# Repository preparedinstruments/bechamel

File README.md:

# Lo-Fi FPGA Video Art Board

A Lattice iCE40HX1K-based FPGA developement board for lo-fi, live-playable video experiments ranging from the gnarly/migraine-inducing all the way to the accidentally enjoyable.

|                          |                          |
:-------------------------:|:-------------------------:
  | 

# Features :

**WARNING: This video may potentially trigger seizures for people with photosensitive epilepsy. Viewer discretion is advised.**

https://github.com/user-attachments/assets/2b71dbfc-7b5e-4651-8198-416c93c0dd36

- 640x480 60Hz HDMI and VGA out, takes raspberry pi video in in DPI mode (https://pinout.xyz/pinout/dpi)
- 9-key mechanical button interface on a hand-solderable, low-cost, single-board design
- 100MHz clock and a 256K x 8 bit external SRAM for screen buffer(s)
- Connections for raspberry pi flash programming

# PCB files

[KiCAD and Eagle PCBs](https://github.com/preparedinstruments/bechamel/tree/main/PCB)

# BOM :

[Excel BOM Mouser / Digikey ](https://github.com/preparedinstruments/bechamel/tree/main/BOM)

- 9x Mechanical keyboard keys
- 1x FPGA iCE40HX1K-TQ144
- 1x 100MHz clock oscillator
- 1x SRAM 2Mb 256Kx8
- 1x Flash N25Q032A13ESC40F
- 1x USB-C SMD 6 pin connector
- 1x 3.3V reg TLV73333PDBVT 
- 1x 1.2V reg TLV73312PDBVT
- 1x PFET
- 1x Resettable Fuse
- 1x D-SUB 15 connector
- 1x HDMI Connector 
- 50x 0.1µF capacitor 0805
- 50x  10kΩ, 1.8kΩ, 1kΩ, 470Ω, 270Ω, 120Ω resistors 0805
- 5x LEDs 0805
- 2x Dual-row headers

optional extras : (1x Raspberry Pi Zero, 1x Micro SD holder, 1x 10kΩ potentiometers)

# HDL files

[Verilog and Pin constraints files ](https://github.com/preparedinstruments/bechamel/tree/main/verilog)

To synthesize files :

[Yoysis Open-source Toolchain ](https://github.com/YosysHQ/yosys)

...or, request an iCEcube2 licence from Lattice :

[iCEcube2 Toolchain](https://www.latticesemi.com/iCEcube2)

To program flash memory you can use raspberry pi using these OLIMEX resources :

- https://www.olimex.com/wiki/ICE40HX1K-EVB#Get_started_under_Linux
- https://github.com/anse1/olimex-ice40-notes

# Raspberry Pi DPI config file

This config file sets the rpi in DPI mode at 50MHz. It can work with the rpi video pass thru verilog file.

[config.txt](https://github.com/preparedinstruments/bechamel/tree/main/raspberry_pi)

# FAQ

Q: How dare you release into the wild verilog code this hideous ?

A: Spank me daddy.

Q: Is this even art ?

A: I can't believe it's not butter! 

# Acknowledgements

**Verilog** :

Mike Field <hamster@snap.net.nz> for his minimalDVID_encoder.vhd : A quick and dirty DVI-D implementation (https://gist.github.com/uXeBoy/0d46e2f1560f73dd573d83e78309bfa0)

Iñigo Muguruza (imuguruza) for his VGA sync code : https://github.com/imuguruza/alhambra_II_test/blob/master/vga/vga_test/vga_sync.v

NightMachines on Bytebeats : https://llllllll.co/t/bytebeats-a-beginner-s-guide/16491

General verilog learning from HDL Bits : https://hdlbits.01xz.net/wiki/Main_Page

**FPGA Hardware design** :

OLIMEX FPGA dev board : https://github.com/OLIMEX/iCE40HX1K-EVB/tree/master

Alhambra II FPGA dev board : https://github.com/FPGAwars/Alhambra-II-FPGA/tree/master

# TODO

Get SD card reading functional

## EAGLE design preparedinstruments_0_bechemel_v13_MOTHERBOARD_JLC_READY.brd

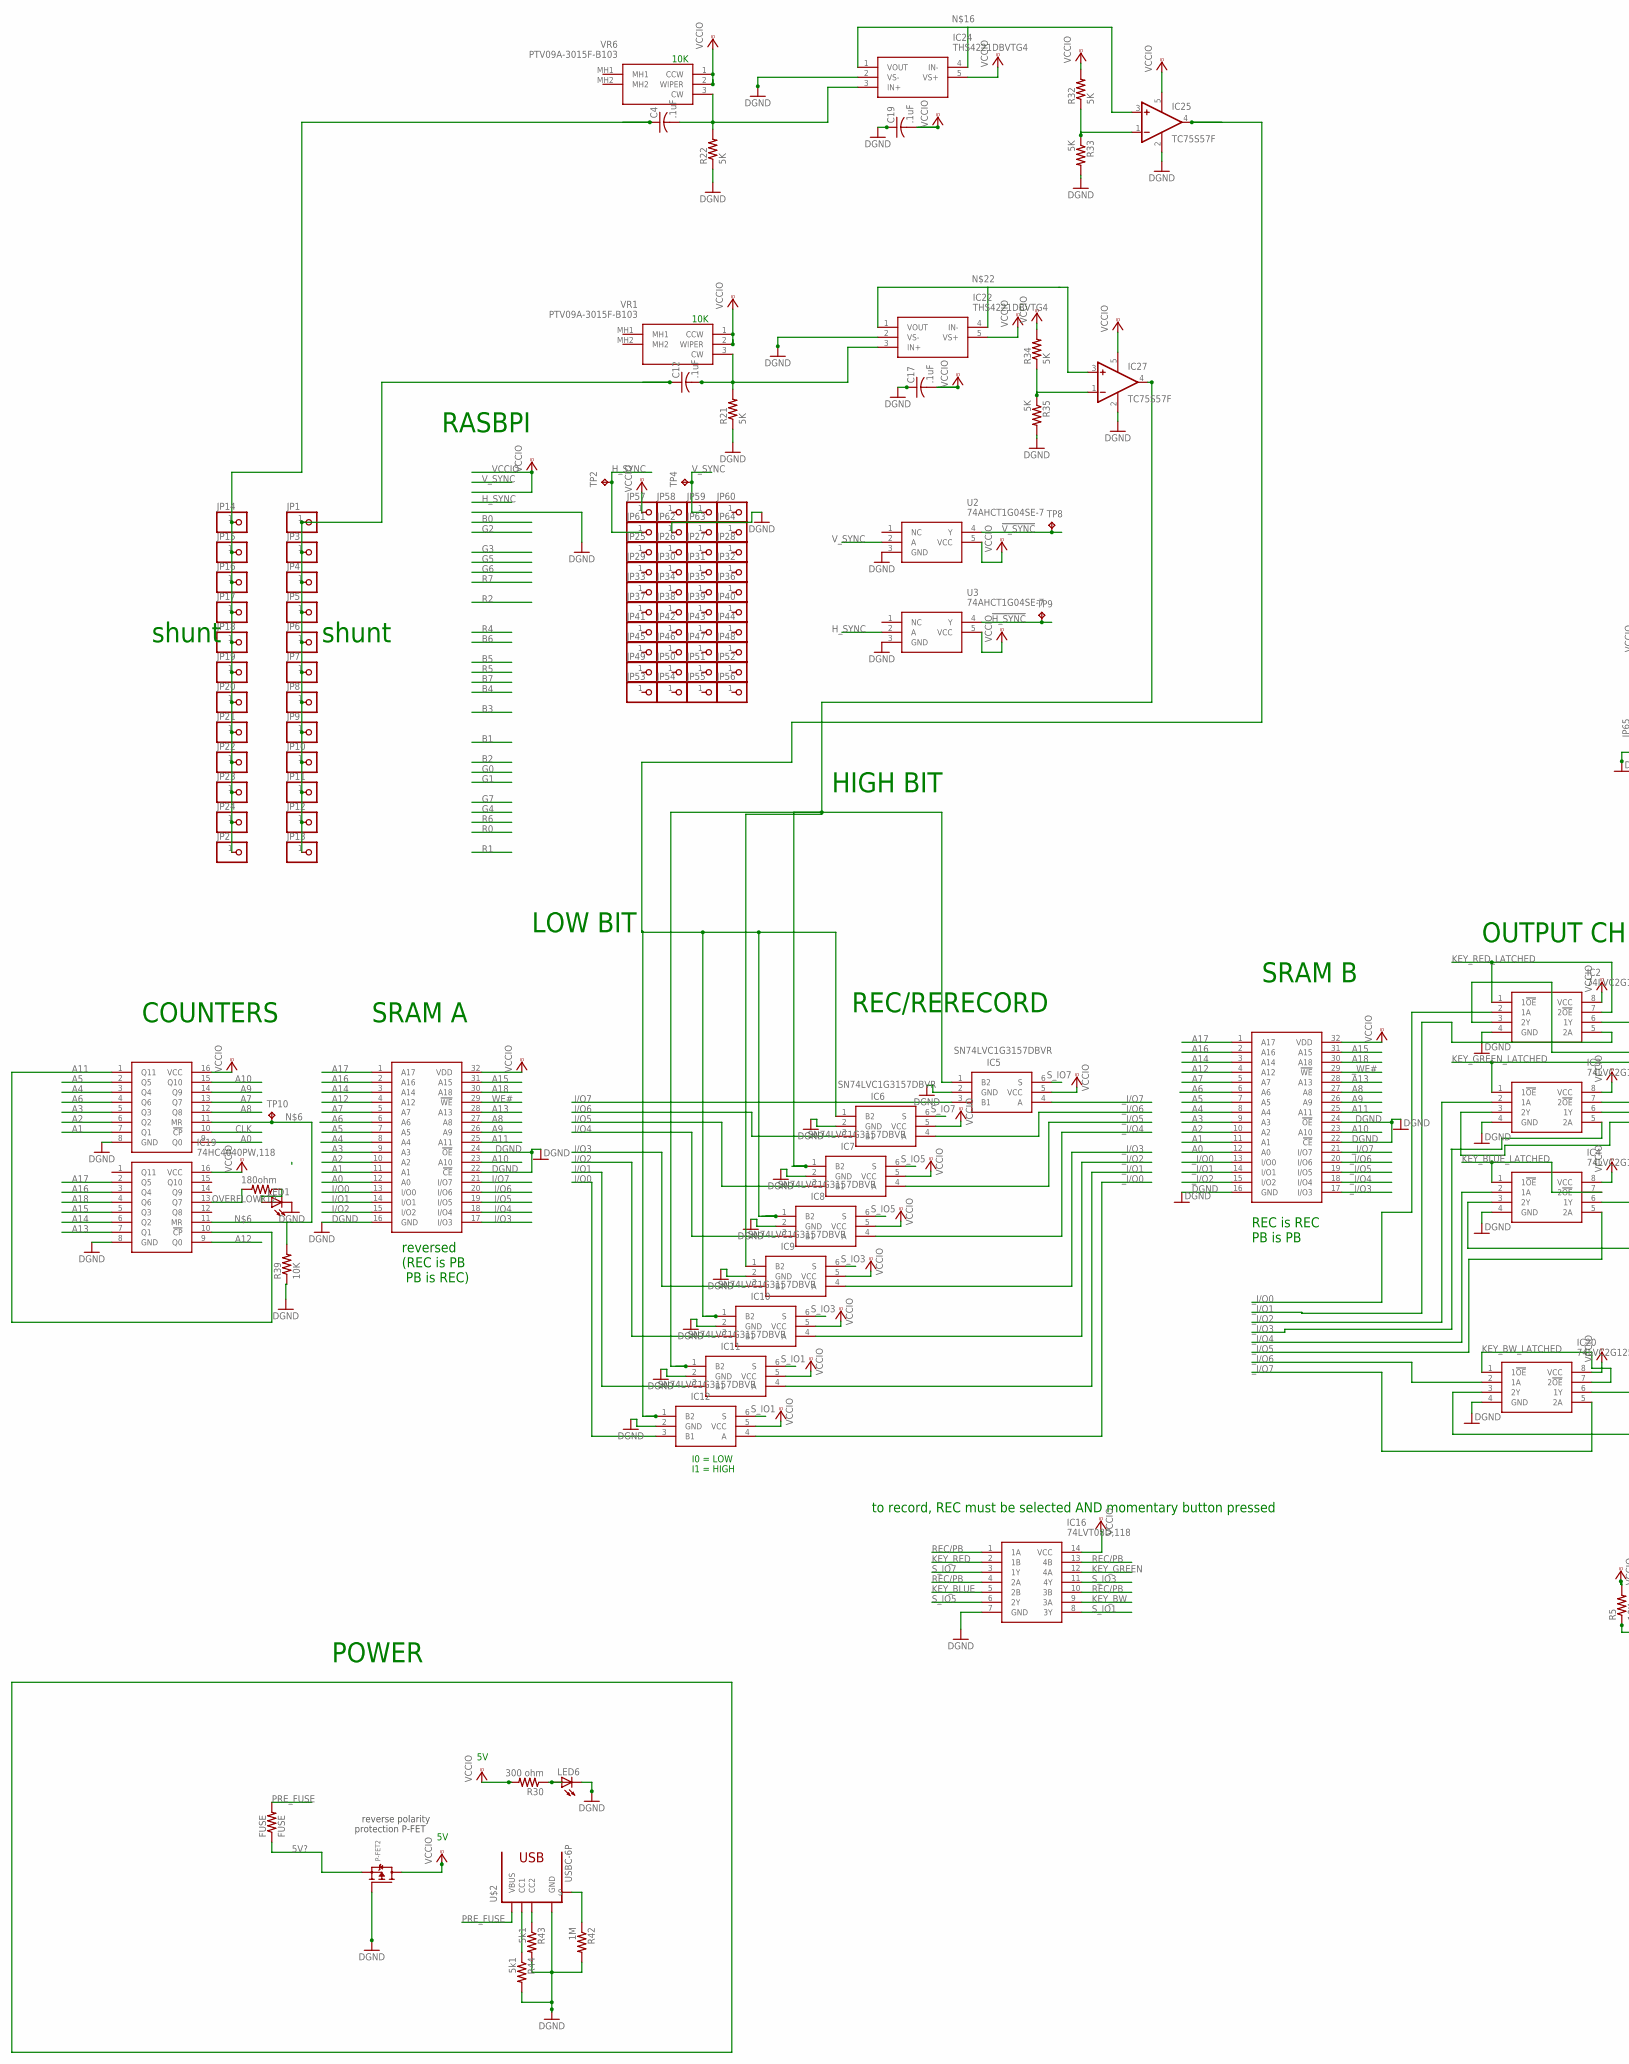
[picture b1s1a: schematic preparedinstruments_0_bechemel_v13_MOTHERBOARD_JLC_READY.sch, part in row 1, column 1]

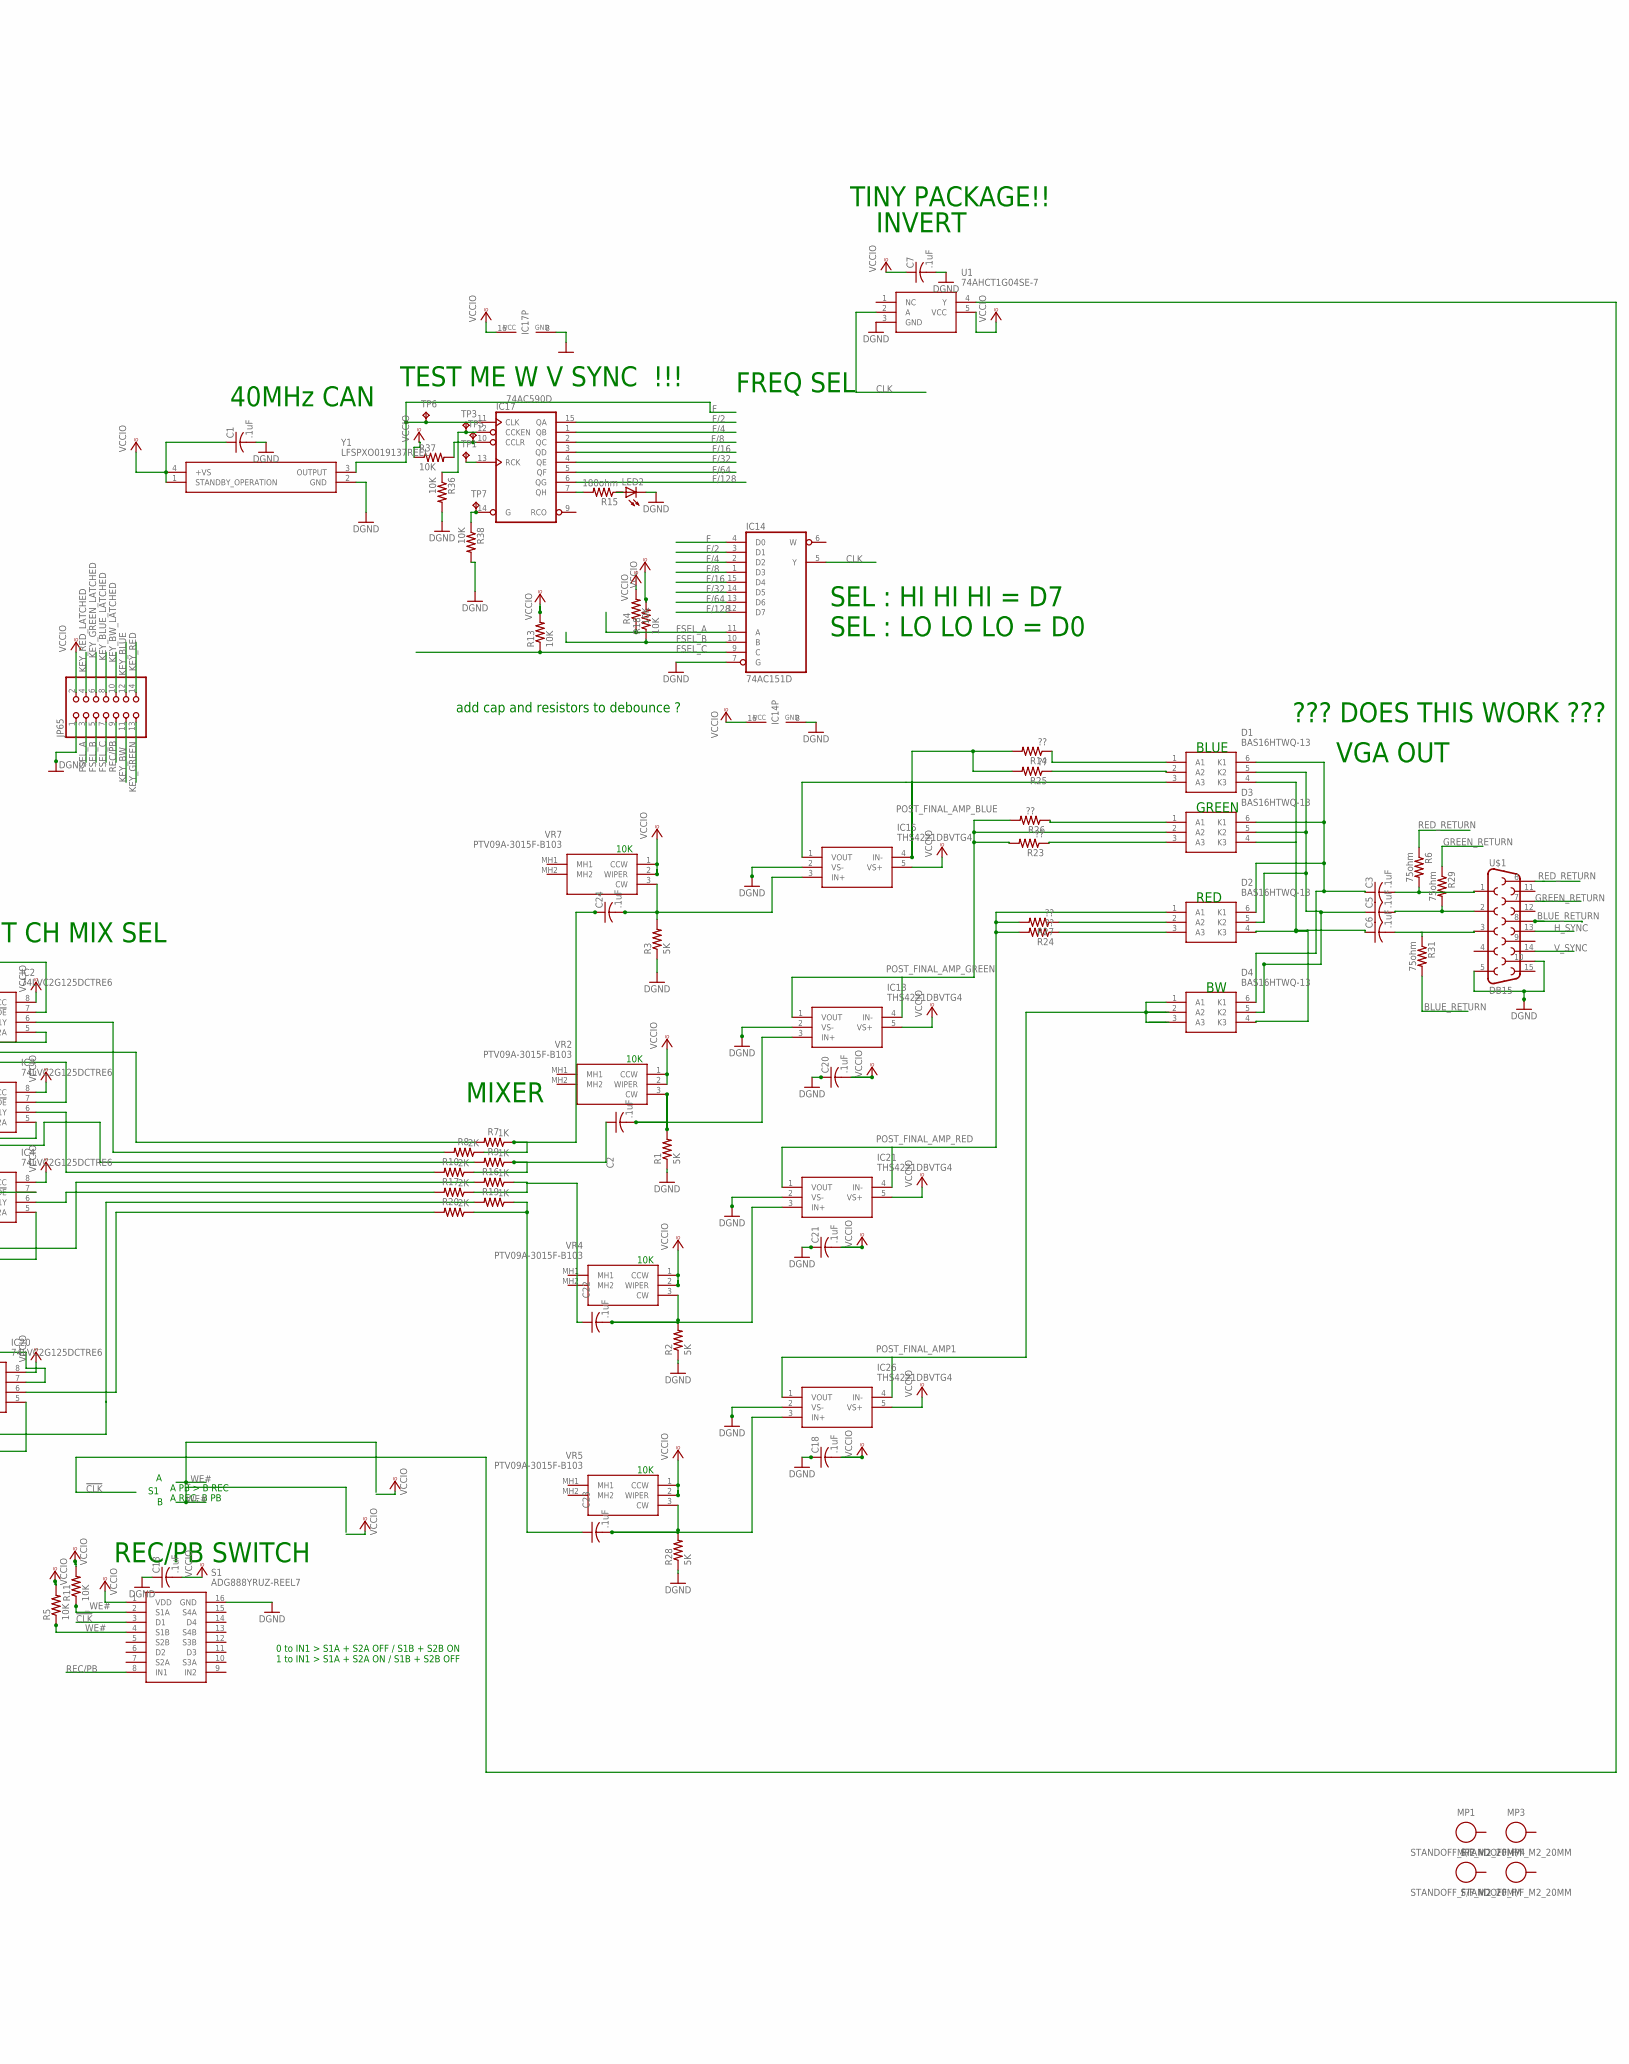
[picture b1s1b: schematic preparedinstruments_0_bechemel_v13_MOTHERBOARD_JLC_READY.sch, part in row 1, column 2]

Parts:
C1, C2, C3, C4, C5, C6, C7, C12, C13, C17, C18, C19, C20, C21, C22, C23, C24: .1uF; C0805
D1, D2, D3, D4: BAS16HTWQ-13; SOT65P210X110-6N
FUSE: FUSE; R0805
IC1, IC23: IS61C5128AS-25QLI; SOIC127P1412X305-32N
IC2, IC3, IC4, IC20: 74LVC2G125DCTRE6; SOP65P400X130-8N
IC5, IC6, IC7, IC8, IC9, IC10, IC11, IC12: SN74LVC1G3157DBVR; SOT95P280X145-6N
IC13, IC15, IC21, IC22, IC24, IC26: THS4221DBVTG4; SOT95P280X145-5N
IC14: 74AC151D; SO16
IC16: 74LVT08D,118; 74LVT08D118
IC17: 74AC590D; SO16
IC18, IC19: 74HC4040PW,118; SOP65P640X110-16N
IC25, IC27: TC75S57F; DBV-R-PDSO-G5
JP1, JP2, JP3, JP4, JP5, JP6, JP7, JP8, JP9, JP10, JP11, JP12, JP13, JP14, JP15, JP16, JP17, JP18, JP19, JP20, JP21, JP22, JP23, JP24, JP25, JP26, JP27, JP28, JP29, JP30, JP31, JP32, JP33, JP34, JP35, JP36, JP37, JP38, JP39, JP40, JP41, JP42, JP43, JP44, JP45, JP46, JP47, JP48, JP49, JP50, JP51, JP52, JP53, JP54, JP55, JP56, JP57, JP58, JP59, JP60, JP61, JP62, JP63, JP64: PINHD-1X1; 1X01
JP65: PINHD-2X7; 2X07
LED1, LED2, LED6: LEDCHIPLED_0805; CHIPLED_0805
MP1, MP2, MP3, MP4: STANDOFF_F/F_M2_20MM; STANDOFF_HEX_FEMALE_400X2000_M2X0.4_MTGP600H220
P-FET2: MOSFET-PWIDE; SOT23-WIDE
R1, R2, R3, R21, R22, R28, R32, R33, R34, R35: 5K; R0805
R4, R5, R11, R13, R18, R36, R37, R38, R39: 10K; R0805
R6, R29, R31: 75ohm; R0805
R7, R9, R16, R19: 1K; R0805
R8, R10, R17, R20: 2K; R0805
R12, R15: 180ohm; R0805
R14, R23, R24, R25, R26, R27: ??; R0805
R30: 300 ohm; R0805
R42: 1M; R0805
R43, R44: 5k1; R0805
S1: ADG888YRUZ-REEL7; SOP65P640X120-16N
TP1, TP2, TP3, TP4, TP5, TP6, TP7, TP8, TP9, TP10: TPB1,27; B1,27
U1, U2, U3: 74AHCT1G04SE-7; SOT65P210X110-5N
U$1: DB15
U$2: USBC-6P; USCX-06FX-XXMX-01
VR1, VR2, VR4, VR5, VR6, VR7: PTV09A-3015F-B103; PTV09A3015FB103
Y1: LFSPXO019137REEL

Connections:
5V?: FUSE.1, P-FET2.2 (S)
!CLK: S1.3 (D1), U1.4 (Y)
!H_SYNC: TP9.TP, U3.4 (Y)
!V_SYNC: TP8.TP, U2.4 (Y)
A0: IC1.12 (A0), IC18.9 (Q0), IC23.12 (A0)
A1: IC1.11 (A1), IC18.7 (Q1), IC23.11 (A1)
A2: IC1.10 (A2), IC18.6 (Q2), IC23.10 (A2)
A3: IC1.9 (A3), IC18.5 (Q3), IC23.9 (A3)
A4: IC1.8 (A4), IC18.3 (Q4), IC23.8 (A4)
A5: IC1.7 (A5), IC18.2 (Q5), IC23.7 (A5)
A6: IC1.6 (A6), IC18.4 (Q6), IC23.6 (A6)
A7: IC1.5 (A7), IC18.13 (Q7), IC23.5 (A7)
A8: IC1.27 (A8), IC18.12 (Q8), IC23.27 (A8)
A9: IC1.26 (A9), IC18.14 (Q9), IC23.26 (A9)
A10: IC1.23 (A10), IC18.15 (Q10), IC23.23 (A10)
A11: IC1.25 (A11), IC18.1 (Q11), IC19.10 (!CP), IC23.25 (A11)
A12: IC1.4 (A12), IC19.9 (Q0), IC23.4 (A12)
A13: IC1.28 (A13), IC19.7 (Q1), IC23.28 (A13)
A14: IC1.3 (A14), IC19.6 (Q2), IC23.3 (A14)
A15: IC1.31 (A15), IC19.5 (Q3), IC23.31 (A15)
A16: IC1.2 (A16), IC19.3 (Q4), IC23.2 (A16)
A17: IC1.1 (A17), IC19.2 (Q5), IC23.1 (A17)
A18: IC1.30 (A18), IC19.4 (Q6), IC23.30 (A18)
BLUE_RETURN: R31.2, U$1.8
CLK: IC14.5 (Y), IC18.10 (!CP), U1.2 (A)
COMP2_OUT: IC6.1 (B2), IC8.1 (B2), IC10.1 (B2), IC12.1 (B2), IC25.4 (OUT)
DGND: C1.2, C7.2, C13.1, C17.1, C18.1, C19.1, C20.1, C21.1, IC1.16 (GND), IC1.22 (!CE), IC1.24 (!OE), IC2.4 (GND), IC3.4 (GND), IC4.4 (GND), IC5.2 (GND), IC6.2 (GND), IC7.2 (GND), IC8.2 (GND), IC9.2 (GND), IC10.2 (GND), IC11.2 (GND), IC12.2 (GND), IC13.2 (VS-), IC14.7 (G), IC14.8 (GND), IC15.2 (VS-), IC16.7 (GND), IC17.8 (GND), IC18.8 (GND), IC19.8 (GND), IC20.4 (GND), IC21.2 (VS-), IC22.2 (VS-), IC23.16 (GND), IC23.22 (!CE), IC23.24 (!OE), IC24.2 (VS-), IC25.2 (GND), IC26.2 (VS-), IC27.2 (GND), JP62.1, JP65.1, LED1.C, LED2.C, LED6.C, P-FET2.1 (G), R1.1, R2.1, R3.1, R21.1, R22.1, R28.1, R33.2, R35.2, R36.2, R38.2, R39.1, R42.2, R43.2, R44.2, S1.16 (GND), U1.3 (GND), U2.3 (GND), U3.3 (GND), U$1.5, U$1.10, U$2.GND1 (GND), U$2.GND2 (GND), Y1.2 (GND)
F: IC14.4 (D0), IC17.11 (CLK), TP6.TP, Y1.3 (OUTPUT)
F/2: IC14.3 (D1), IC17.15 (QA)
F/4: IC14.2 (D2), IC17.1 (QB)
F/8: IC14.1 (D3), IC17.2 (QC)
F/16: IC14.15 (D4), IC17.3 (QD)
F/32: IC14.14 (D5), IC17.4 (QE)
F/64: IC14.13 (D6), IC17.5 (QF)
F/128: IC14.12 (D7), IC17.6 (QG)
FSEL_A: IC14.11 (A), JP65.3, R4.1
FSEL_B: IC14.10 (B), JP65.5, R18.1
FSEL_C: IC14.9 (C), JP65.7, R13.1
GREEN_RETURN: R29.1, U$1.7
H_SYNC: JP61.1, TP2.TP, U3.2 (A), U$1.13
I/O0: IC12.3 (B1), IC23.13 (I/O0)
I/O1: IC11.3 (B1), IC23.14 (I/O1)
I/O2: IC10.3 (B1), IC23.15 (I/O2)
I/O3: IC9.3 (B1), IC23.17 (I/O3)
I/O4: IC8.3 (B1), IC23.18 (I/O4)
I/O5: IC7.3 (B1), IC23.19 (I/O5)
I/O6: IC6.3 (B1), IC23.20 (I/O6)
I/O7: IC5.3 (B1), IC23.21 (I/O7)
INT_IN1: C24.2, IC15.3 (IN+), R3.2, VR7.3 (CW)
INT_IN2: C12.2, IC22.3 (IN+), R21.2, VR1.3 (CW)
INT_IN3: C4.2, IC24.3 (IN+), R22.2, VR6.3 (CW)
INT_IN4: C22.2, IC21.3 (IN+), R2.2, VR4.3 (CW)
INT_IN5: C23.2, IC26.3 (IN+), R28.2, VR5.3 (CW)
INT_IN6: C2.2, IC13.3 (IN+), R1.2, VR2.3 (CW)
KEY_BLUE: IC16.5 (2B), JP65.12
KEY_BLUE_LATCHED: IC4.1 (1!OE), IC4.7 (2!OE), JP65.8
KEY_BW: IC16.9 (3A), JP65.11
KEY_BW_LATCHED: IC20.1 (1!OE), IC20.7 (2!OE), JP65.10
KEY_GREEN: IC16.12 (4A), JP65.13
KEY_GREEN_LATCHED: IC3.1 (1!OE), IC3.7 (2!OE), JP65.6
KEY_RED: IC16.2 (1B), JP65.14
KEY_RED_LATCHED: IC2.1 (1!OE), IC2.7 (2!OE), JP65.4
unnamed: LED2.A, R15.1
unnamed: C3.2, R6.2, U$1.1
unnamed: C12.1, JP1.1, JP3.1, JP4.1, JP5.1, JP6.1, JP7.1, JP8.1, JP9.1, JP10.1, JP11.1, JP12.1, JP13.1
unnamed: LED1.A, R12.1
unnamed: IC17.7 (QH), R15.2
unnamed: IC18.11 (MR), IC19.11 (MR), R39.2, TP10.TP
unnamed: IC4.3 (2Y), R16.2
unnamed: C5.2, R29.2, U$1.2
unnamed: LED6.A, R30.1
unnamed: IC4.6 (1Y), R17.2
unnamed: C6.2, R31.1, U$1.3
unnamed: R43.1, U$2.CC2
unnamed: IC25.1 (-IN), R32.1, R33.1
unnamed: IC24.1 (VOUT), IC24.4 (IN-), IC25.3 (+IN)
unnamed: IC20.3 (2Y), R19.2
unnamed: R42.1, U$2.SHIELD1 (S), U$2.SHIELD2 (S), U$2.SHIELD3 (S), U$2.SHIELD4 (S)
unnamed: IC27.1 (-IN), R34.1, R35.1
unnamed: IC20.6 (1Y), R20.2
unnamed: R44.1, U$2.CC1
unnamed: IC22.1 (VOUT), IC22.4 (IN-), IC27.3 (+IN)
unnamed: IC17.12 (CCKEN), R36.1, TP3.TP
unnamed: IC2.3 (2Y), R7.2
unnamed: IC2.6 (1Y), R8.2
unnamed: IC3.3 (2Y), R9.2
unnamed: IC3.6 (1Y), R10.2
unnamed: C4.1, JP2.1, JP14.1, JP15.1, JP16.1, JP17.1, JP18.1, JP19.1, JP20.1, JP21.1, JP22.1, JP23.1, JP24.1
unnamed: IC17.13 (RCK), TP1.TP
unnamed: IC17.10 (CCLR), R37.2, TP5.TP
unnamed: C24.1, R7.1, R8.1
unnamed: C22.1, R16.1, R17.1
unnamed: C2.1, R9.1, R10.1
unnamed: C23.1, R19.1, R20.1
unnamed: D3.1 (A1), R26.1
unnamed: D1.1 (A1), R14.1
unnamed: D1.2 (A2), R25.1
unnamed: D2.3 (A3), R24.1
unnamed: C3.1, D1.6 (K1), D2.6 (K1), D3.6 (K1), D4.6 (K1)
unnamed: IC17.14 (G), R38.1, TP7.TP
unnamed: D2.2 (A2), R27.1
unnamed: D3.3 (A3), R23.1
unnamed: C5.1, D1.5 (K2), D2.5 (K2), D3.5 (K2), D4.5 (K2)
unnamed: C6.1, D1.4 (K3), D2.4 (K3), D3.4 (K3), D4.4 (K3)
OVERFLOW: IC19.13 (Q7), R12.2
POST_FINAL_AMP1: D4.1 (A1), D4.2 (A2), D4.3 (A3), IC26.1 (VOUT), IC26.4 (IN-)
POST_FINAL_AMP_BLUE: D1.3 (A3), IC15.1 (VOUT), IC15.4 (IN-), R14.2, R25.2
POST_FINAL_AMP_GREEN: D3.2 (A2), IC13.1 (VOUT), IC13.4 (IN-), R23.2, R26.2
POST_FINAL_AMP_RED: D2.1 (A1), IC21.1 (VOUT), IC21.4 (IN-), R24.2, R27.2
PRE_FUSE: FUSE.2, U$2.VBUS1 (VBUS), U$2.VBUS2 (VBUS)
REC/PB: IC16.1 (1A), IC16.4 (2A), IC16.10 (3B), IC16.13 (4B), JP65.9, S1.8 (IN1)
RED_RETURN: R6.1, U$1.6
S_IO1: IC11.6 (S), IC12.6 (S), IC16.8 (3Y)
S_IO3: IC9.6 (S), IC10.6 (S), IC16.11 (4Y)
S_IO5: IC7.6 (S), IC8.6 (S), IC16.6 (2Y)
S_IO7: IC5.6 (S), IC6.6 (S), IC16.3 (1Y)
VCCIO: C1.1, C7.1, C13.2, C17.2, C18.2, C19.2, C20.2, C21.2, IC1.32 (VDD), IC2.8 (VCC), IC3.8 (VCC), IC4.8 (VCC), IC5.5 (VCC), IC6.5 (VCC), IC7.5 (VCC), IC8.5 (VCC), IC9.5 (VCC), IC10.5 (VCC), IC11.5 (VCC), IC12.5 (VCC), IC13.5 (VS+), IC14.16 (VCC), IC15.5 (VS+), IC16.14 (VCC), IC17.16 (VCC), IC18.16 (VCC), IC19.16 (VCC), IC20.8 (VCC), IC21.5 (VS+), IC22.5 (VS+), IC23.32 (VDD), IC24.5 (VS+), IC25.5 (V+), IC26.5 (VS+), IC27.5 (V+), JP57.1, JP65.2, P-FET2.3 (D), R4.2, R5.2, R11.2, R13.2, R18.2, R30.2, R32.2, R34.2, R37.1, S1.1 (VDD), U1.5 (VCC), U2.5 (VCC), U3.5 (VCC), VR1.1 (CCW), VR1.2 (WIPER), VR2.1 (CCW), VR2.2 (WIPER), VR4.1 (CCW), VR4.2 (WIPER), VR5.1 (CCW), VR5.2 (WIPER), VR6.1 (CCW), VR6.2 (WIPER), VR7.1 (CCW), VR7.2 (WIPER), Y1.1 (STANDBY_OPERATION), Y1.4 (+VS)
V_SYNC: JP59.1, TP4.TP, U2.2 (A), U$1.14
WE#: IC23.29 (!WE), R5.1, S1.4 (S1B)
_COMP2_OUT: IC5.1 (B2), IC7.1 (B2), IC9.1 (B2), IC11.1 (B2), IC27.4 (OUT)
_I/O0: IC1.13 (I/O0), IC2.2 (1A), IC12.4 (A)
_I/O1: IC1.14 (I/O1), IC2.5 (2A), IC11.4 (A)
_I/O2: IC1.15 (I/O2), IC3.2 (1A), IC10.4 (A)
_I/O3: IC1.17 (I/O3), IC3.5 (2A), IC9.4 (A)
_I/O4: IC1.18 (I/O4), IC4.2 (1A), IC8.4 (A)
_I/O5: IC1.19 (I/O5), IC4.5 (2A), IC7.4 (A)
_I/O6: IC1.20 (I/O6), IC6.4 (A), IC20.2 (1A)
_I/O7: IC1.21 (I/O7), IC5.4 (A), IC20.5 (2A)
_WE#: IC1.29 (!WE), R11.1, S1.2 (S1A)

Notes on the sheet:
I0 = LOW
I1 = HIGH
FREQ SEL
A PB > B REC
A REC, B PB
MIXER
REC/RERECORD
COUNTERS
SRAM A
SRAM B
VGA OUT
OUTPUT CH MIX SEL
40MHz CAN
INVERT
10K
reversed (REC is PB PB is REC)
REC is REC PB is PB
POWER
reverse polarity
protection P-FET
add cap and resistors to debounce ?
RASBPI
shunt
HIGH BIT
LOW BIT
TINY PACKAGE!!
REC/PB SWITCH
0 to IN1 > S1A + S2A OFF / S1B + S2B ON 1 to IN1 > S1A + S2A ON / S1B + S2B OFF
??? DOES THIS WORK ???
to record, REC must be selected AND momentary button pressed
GREEN
BLUE
RED
TEST ME W V SYNC !!!
SEL : HI HI HI = D7 SEL : LO LO LO = D0

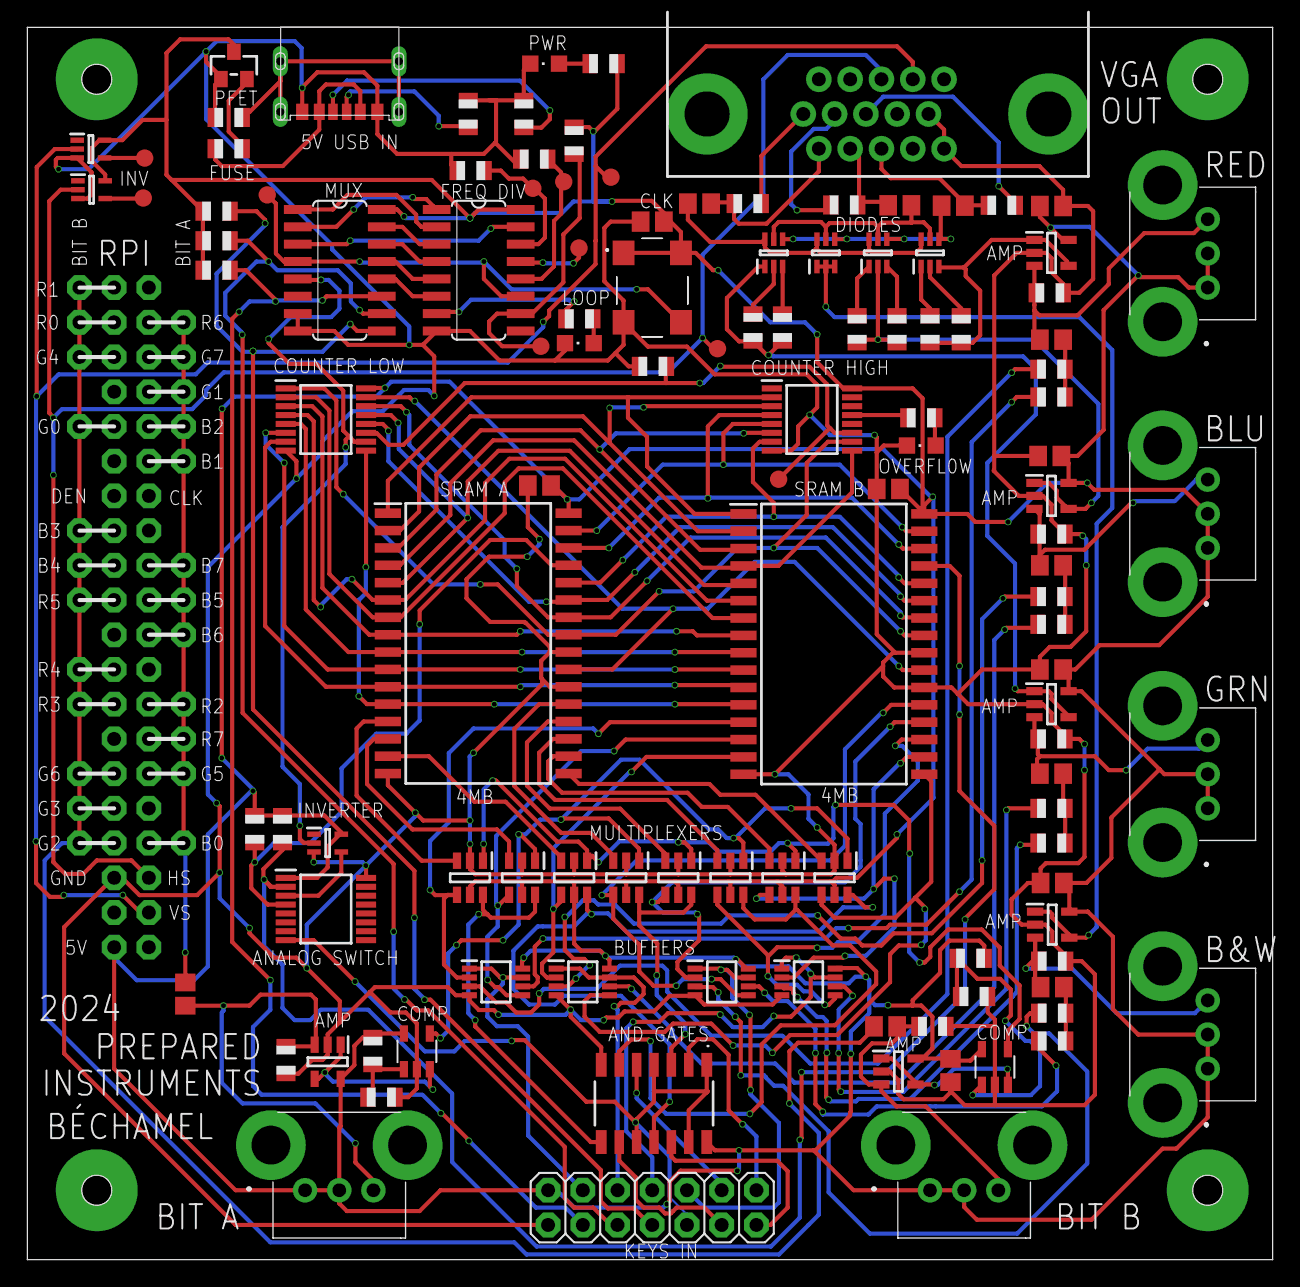
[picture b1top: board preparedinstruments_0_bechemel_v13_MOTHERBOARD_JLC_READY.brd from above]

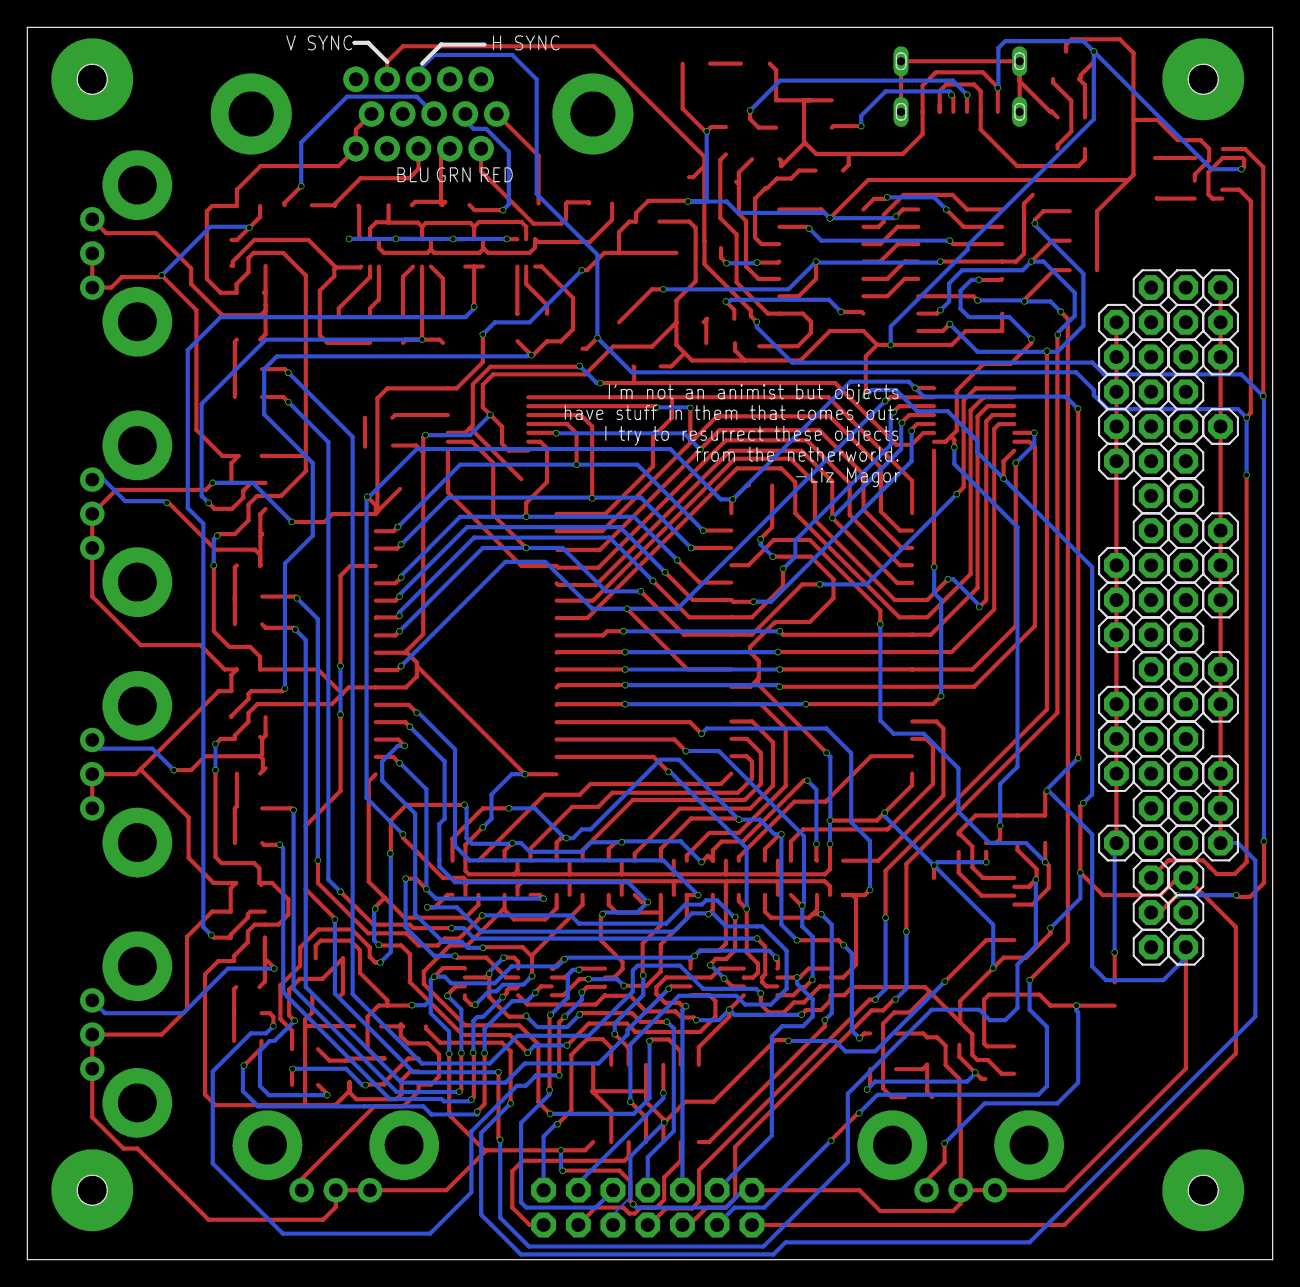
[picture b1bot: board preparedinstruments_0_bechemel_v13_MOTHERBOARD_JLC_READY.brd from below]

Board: 2 copper layers, 91.1 x 90.2 mm, 187 parts (64 on the bottom side), 129 nets.

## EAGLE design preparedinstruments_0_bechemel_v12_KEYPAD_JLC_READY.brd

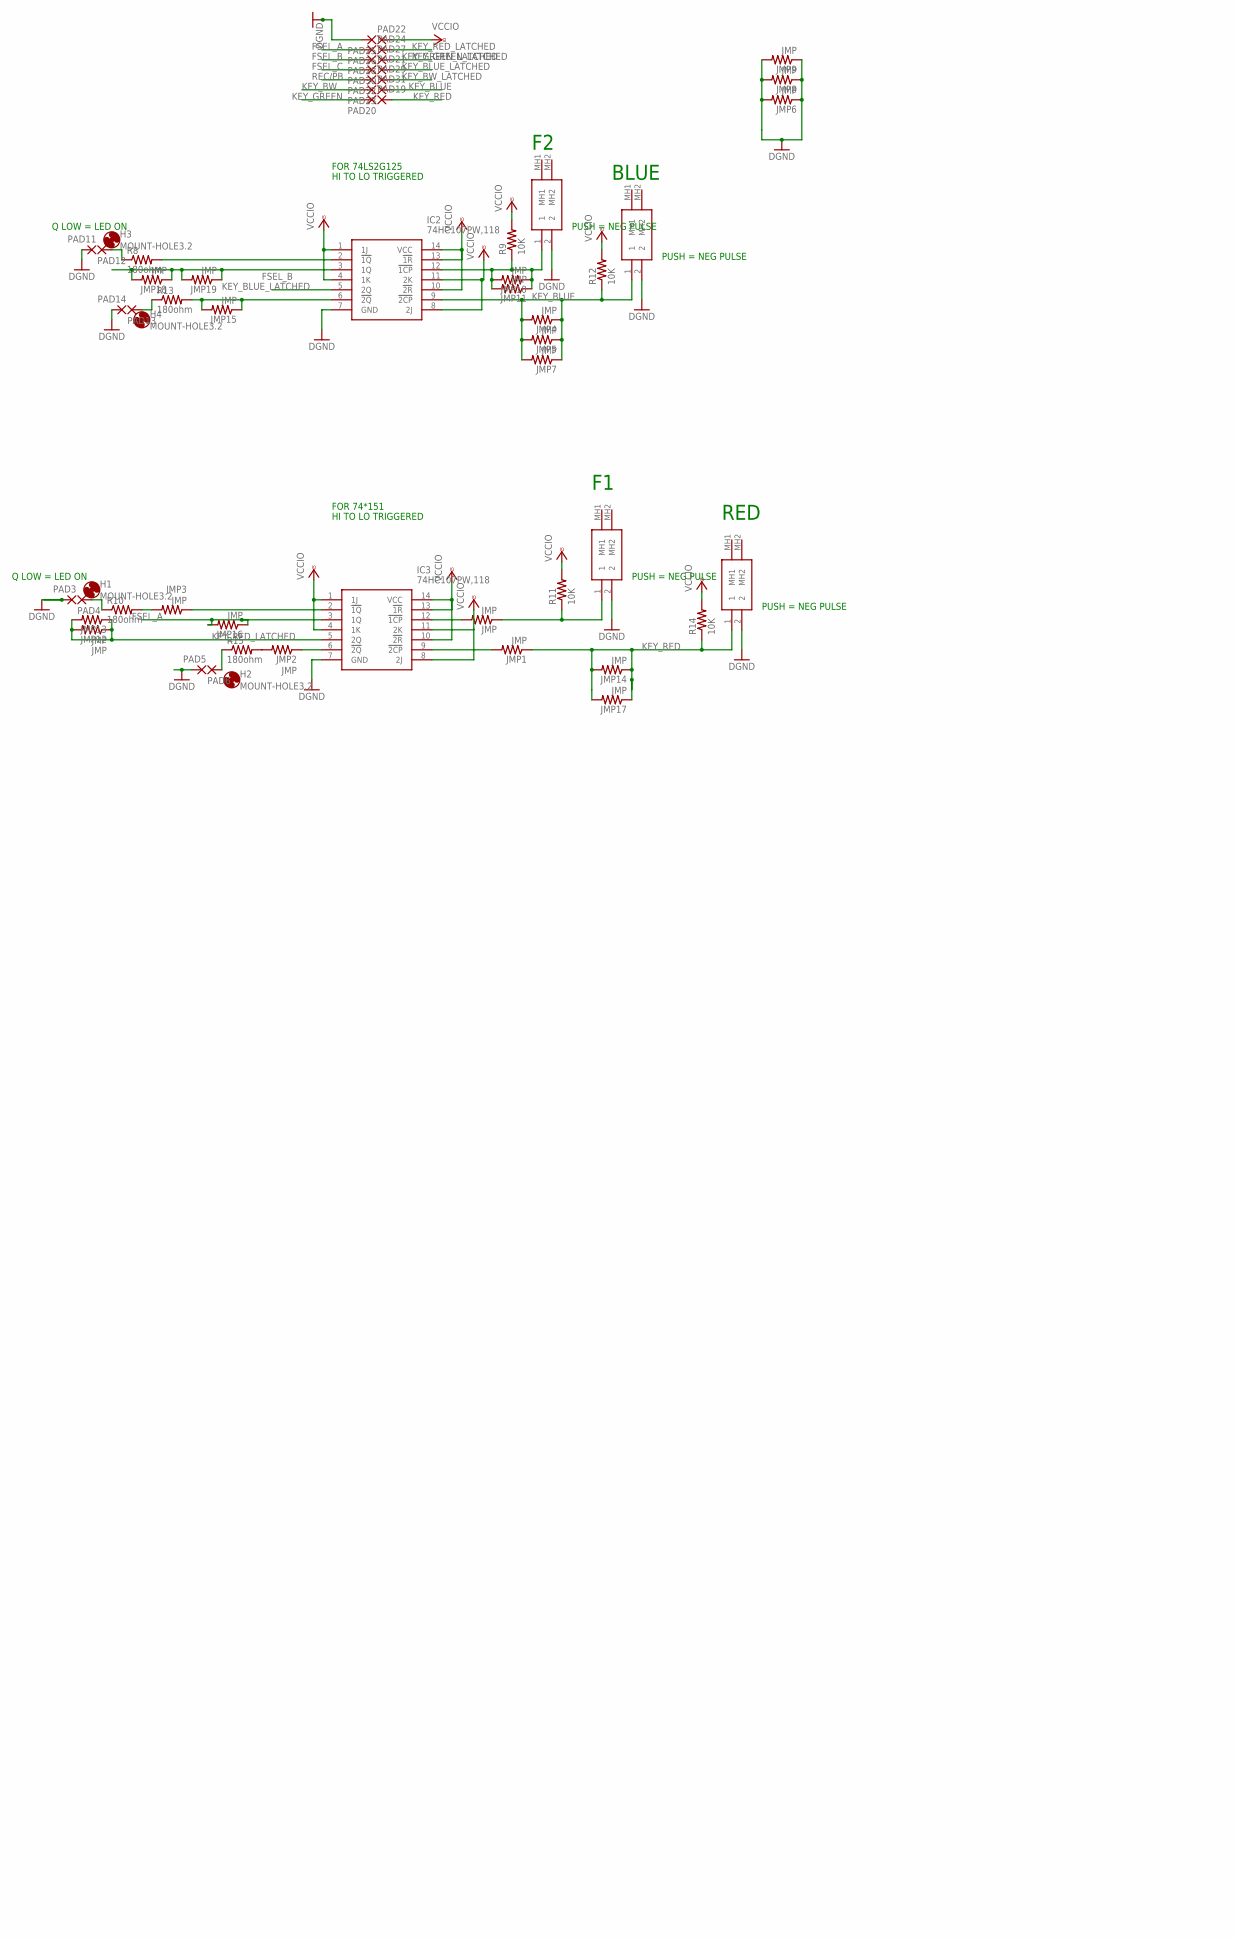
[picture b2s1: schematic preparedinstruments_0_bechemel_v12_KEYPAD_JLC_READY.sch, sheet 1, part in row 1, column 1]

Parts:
H1, H2, H3, H4: MOUNT-HOLE3.2; 3,2
IC2, IC3: 74HC107PW,118; SOP65P640X110-14N
JMP, JMP1, JMP2, JMP3, JMP4, JMP5, JMP6, JMP7, JMP8, JMP9, JMP10, JMP11, JMP12, JMP13, JMP14, JMP15, JMP16, JMP17, JMP18, JMP19: JMP; R0805
MP1, MP2, MP3, MP4: STANDOFF_F/F_M2_20MM; STANDOFF_HEX_FEMALE_400X2000_M2X0.4_MTGP600H220
PAD3, PAD4, PAD5, PAD6, PAD11, PAD12, PAD13, PAD14, PAD19, PAD20, PAD21, PAD22, PAD23, PAD24, PAD25, PAD26, PAD27, PAD28, PAD29, PAD30, PAD31, PAD32: SMD2; SMD1,27-2,54
R8, R10, R13, R15: 180ohm; R0805
R9, R11, R12, R14: 10K; R0805
S6, S7, S8, S9: MX1A-11NW; MX1A11NW

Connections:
DGND: IC2.7 (GND), IC3.7 (GND), JMP6.1, JMP6.2, JMP8.1, JMP8.2, JMP9.1, JMP9.2, PAD3.1, PAD5.1, PAD11.1, PAD14.1, PAD25.1, S6.2, S7.2, S8.2, S9.2; also elsewhere on the board
FSEL_A: IC3.3 (1Q), JMP16.1, JMP16.2, PAD26.1
FSEL_B: IC2.3 (1Q), JMP18.1, JMP18.2, JMP19.1, JMP19.2, PAD28.1
FSEL_C: PAD30.1; also elsewhere on the board
KEY_BLUE: IC2.9 (!2CP), JMP4.1, JMP4.2, JMP5.1, JMP5.2, JMP7.1, JMP7.2, PAD31.1, R12.1, S8.1
KEY_BLUE_LATCHED: IC2.5 (2Q), PAD21.1
KEY_BW: PAD23.1; also elsewhere on the board
KEY_BW_LATCHED: PAD29.1; also elsewhere on the board
KEY_GREEN: PAD20.1; also elsewhere on the board
KEY_GREEN_LATCHED: PAD27.1; also elsewhere on the board
KEY_RED: JMP1.1, JMP14.1, JMP14.2, JMP17.1, JMP17.2, PAD19.1, R14.1, S9.1
KEY_RED_LATCHED: IC3.5 (2Q), JMP12.1, JMP12.2, JMP13.1, JMP13.2, PAD24.1
unnamed: PAD12.1, R8.1
unnamed: IC2.2 (!1Q), R8.2
unnamed: IC2.12 (!1CP), JMP10.1, JMP10.2, JMP11.1, JMP11.2, R9.1, S6.1
unnamed: PAD4.1, R10.1
unnamed: JMP3.2, R10.2
unnamed: IC3.12 (!1CP), JMP.2
unnamed: PAD13.1, R13.1
unnamed: IC2.6 (!2Q), JMP15.1, JMP15.2, R13.2
unnamed: PAD6.1, R15.1
unnamed: JMP2.2, R15.2
unnamed: JMP.1, R11.1, S7.1
unnamed: IC3.9 (!2CP), JMP1.2
unnamed: IC3.6 (!2Q), JMP2.1
unnamed: IC3.2 (!1Q), JMP3.1
REC/PB: PAD32.1; also elsewhere on the board
VCCIO: IC2.1 (1J), IC2.4 (1K), IC2.8 (2J), IC2.10 (!2R), IC2.11 (2K), IC2.13 (!1R), IC2.14 (VCC), IC3.1 (1J), IC3.4 (1K), IC3.8 (2J), IC3.10 (!2R), IC3.11 (2K), IC3.13 (!1R), IC3.14 (VCC), PAD22.1, R9.2, R11.2, R12.2, R14.2; also elsewhere on the board

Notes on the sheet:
HI TO LO TRIGGERED
PUSH = NEG PULSE
Q LOW = LED ON
FOR 74LS2G125
FOR 74*151
RED
BLUE

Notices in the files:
README.md:
License: MIT
parts and their libraries:
microbuilder: This work is placed in the public domain, and may be freely used for commercial and non-commercial work with the following conditions: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
SparkFun-Retired: Licensing: Creative Commons ShareAlike 4.0 International - https://creativecommons.org/licenses/by-sa/4.0
